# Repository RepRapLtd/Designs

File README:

This is just a dump of all my various designs for things that are not
specifically RepRap.

Some of the things here are OS designs that are not mine, and have just been placed
in this directory by me for convenience.

AB
24/2/2015

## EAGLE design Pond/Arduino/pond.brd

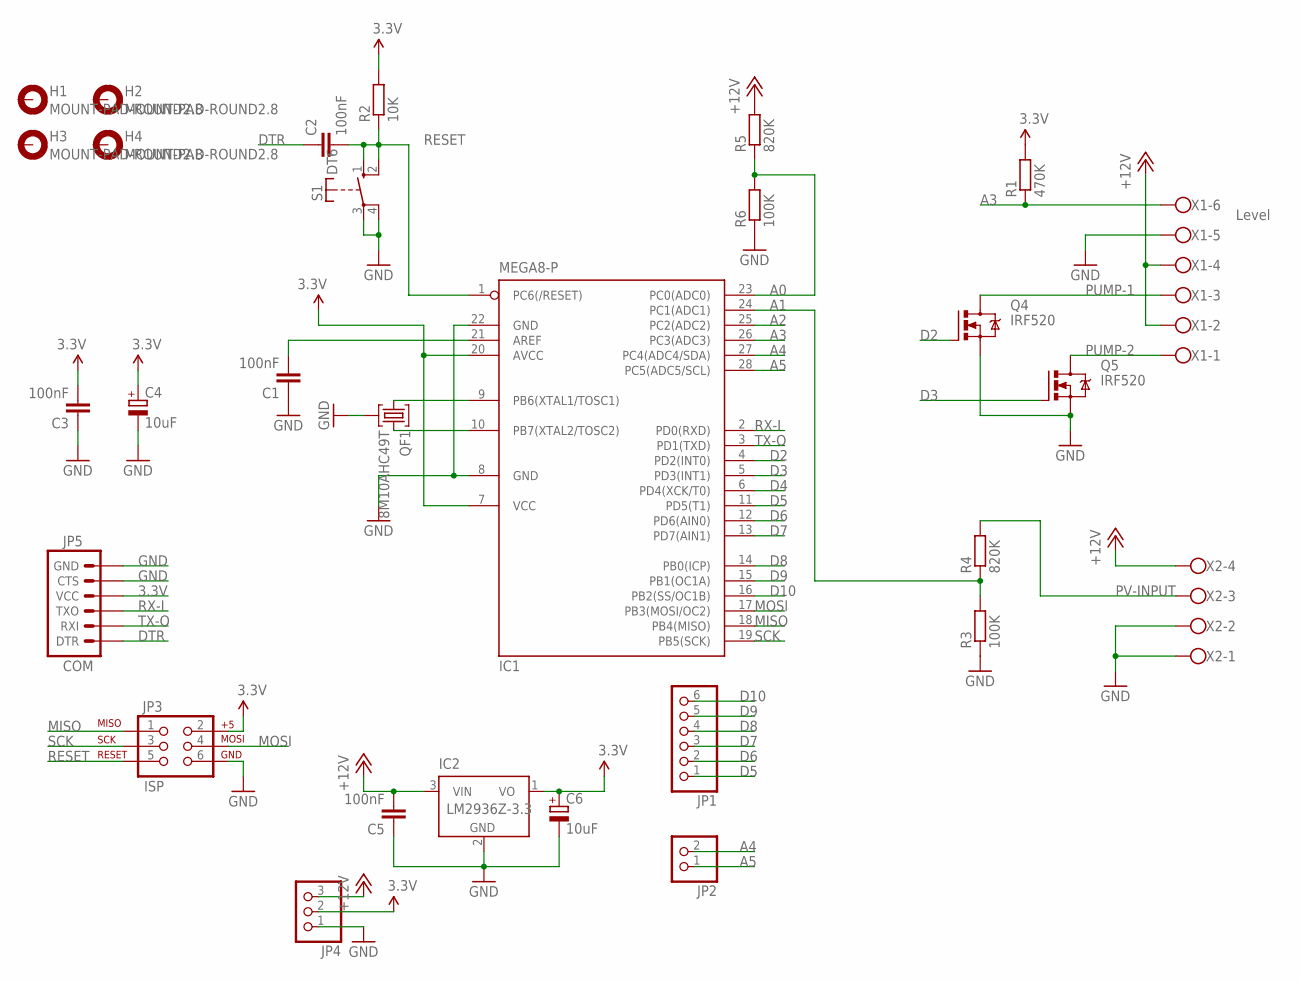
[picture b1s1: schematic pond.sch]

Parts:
C1, C2, C3, C5: 100nF; C050-050X075
C4, C6: 10uF; E2,5-6E
H1, H2, H3, H4: MOUNT-PAD-ROUND2.8; 2,8-PAD
IC1: MEGA8-P; DIL28-3
IC2: LM2936Z-3.3; TO92
JP1: PINHD-1X6; 1X06
JP2: PINHD-1X2; 1X02
JP3: ISP; 2X3
JP4: PINHD-1X3; 1X03
JP5: COM; 1X06
Q4, Q5: IRF520; TO220BV
QF1: 8M10AHC49T; HC49U
R1: 470K; 0207/10
R2: 10K; 0207/10
R3, R6: 100K; 0207/10
R4, R5: 820K; 0207/10
S1: DT6
X1: W237-6
X2: W237-4

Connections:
3.3V: C3.2, C4.+, C6.+, IC1.7 (VCC), IC1.20 (AVCC), IC2.1 (VO), JP3.2, JP4.2, JP5.4 (VCC), R1.2, R2.2
+12V: C5.2, IC2.3 (VIN), JP4.3, R5.2, X1.2, X1.4, X2.4
A0: IC1.23 (PC0(ADC0)), R5.1, R6.2
A1: IC1.24 (PC1(ADC1)), R3.2, R4.1
A2: IC1.25 (PC2(ADC2))
A3: IC1.26 (PC3(ADC3)), R1.1, X1.6
A4: IC1.27 (PC4(ADC4/SDA)), JP2.2
A5: IC1.28 (PC5(ADC5/SCL)), JP2.1
D2: IC1.4 (PD2(INT0)), Q4.G
D3: IC1.5 (PD3(INT1)), Q5.G
D4: IC1.6 (PD4(XCK/T0))
D5: IC1.11 (PD5(T1)), JP1.1
D6: IC1.12 (PD6(AIN0)), JP1.2
D7: IC1.13 (PD7(AIN1)), JP1.3
D8: IC1.14 (PB0(ICP)), JP1.4
D9: IC1.15 (PB1(OC1A)), JP1.5
D10: IC1.16 (PB2(SS/OC1B)), JP1.6
DTR: C2.1, JP5.1 (DTR)
GND: C1.1, C3.1, C4.-, C5.1, C6.-, IC1.8 (GND), IC1.22 (GND), IC2.2 (GND), JP3.6, JP4.1, JP5.5 (CTS), JP5.6 (GND), Q4.S, Q5.S, QF1.2, R3.1, R6.1, S1.3, S1.4, X1.5, X2.1, X2.2
MISO: IC1.18 (PB4(MISO)), JP3.1
MOSI: IC1.17 (PB3(MOSI/OC2)), JP3.4
unnamed: IC1.9 (PB6(XTAL1/TOSC1)), QF1.1
unnamed: IC1.10 (PB7(XTAL2/TOSC2)), QF1.3
unnamed: C1.2, IC1.21 (AREF)
PUMP-1: Q4.D, X1.3
PUMP-2: Q5.D, X1.1
PV-INPUT: R4.2, X2.3
RESET: C2.2, IC1.1 (PC6(/RESET)), JP3.5, R2.1, S1.1 (S), S1.2 (S)
RX-I: IC1.2 (PD0(RXD)), JP5.3 (TXO)
SCK: IC1.19 (PB5(SCK)), JP3.3
TX-O: IC1.3 (PD1(TXD)), JP5.2 (RXI)

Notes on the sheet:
Level

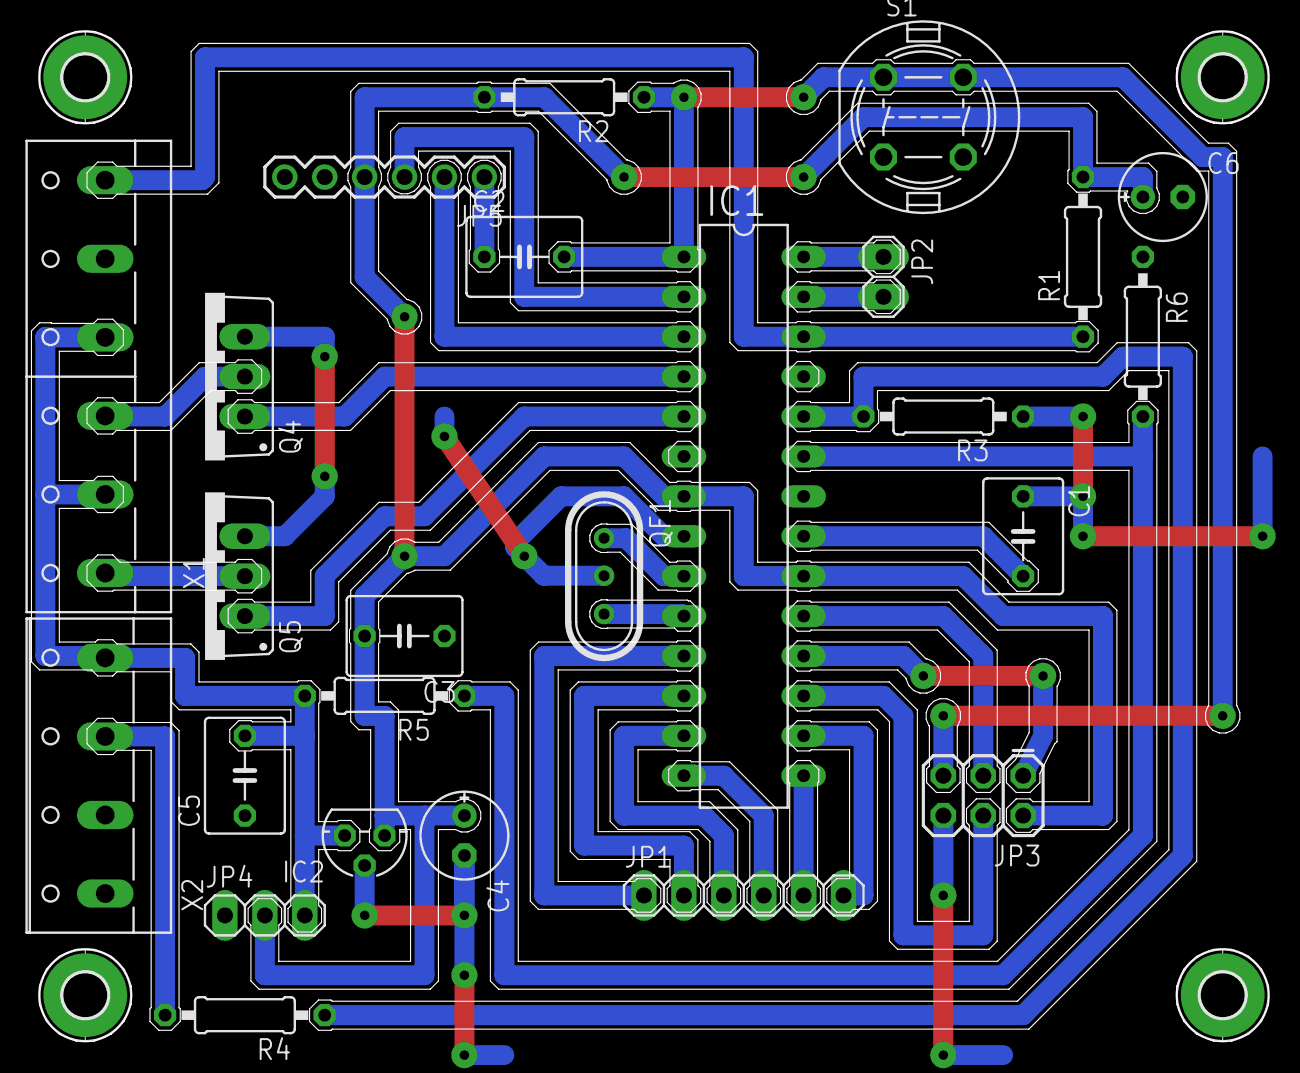
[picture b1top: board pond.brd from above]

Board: 2 copper layers, 78.7 x 64.3 mm, 29 parts (0 on the bottom side), 29 nets.

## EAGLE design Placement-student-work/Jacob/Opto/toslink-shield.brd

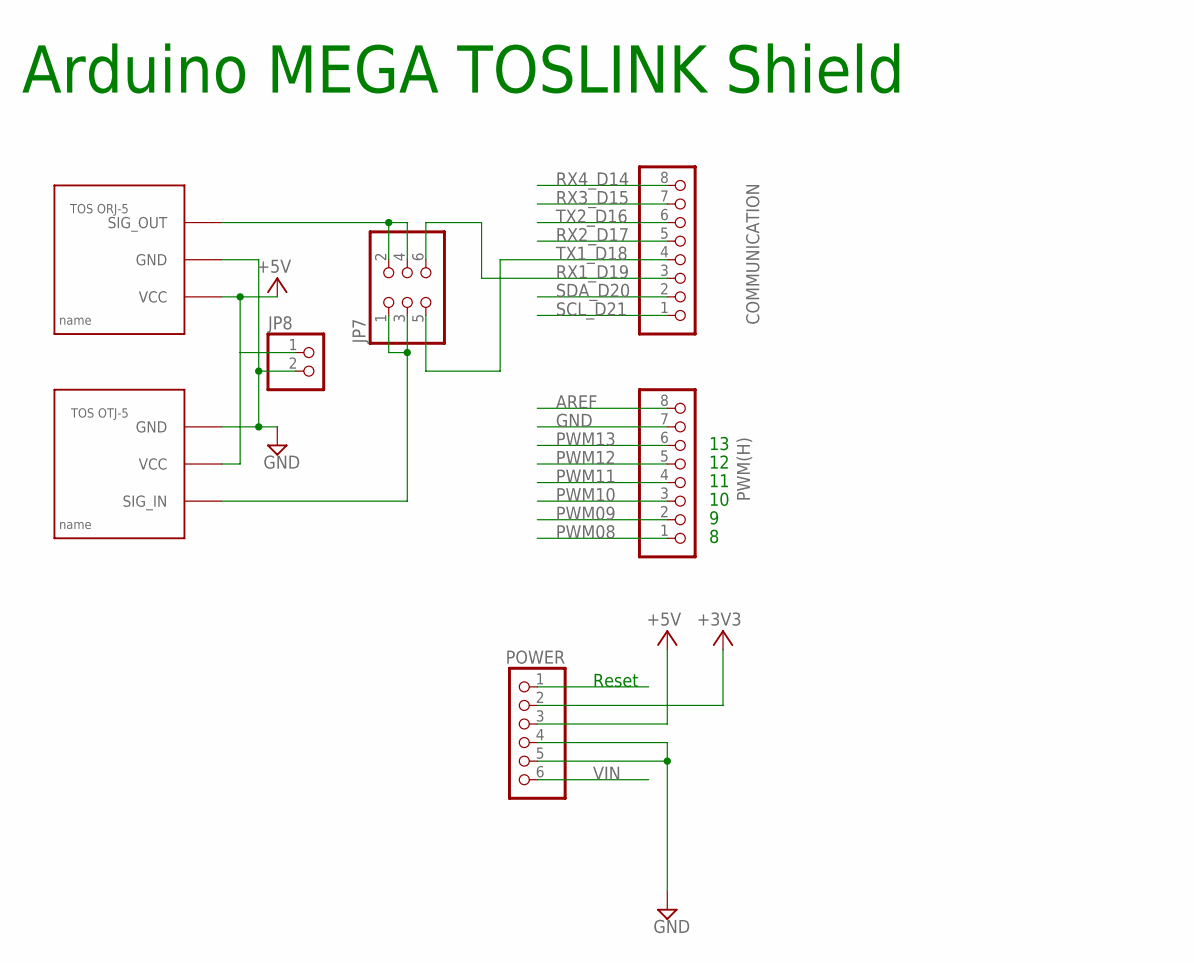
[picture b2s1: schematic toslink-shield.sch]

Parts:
COMMUNICATION: PINHD-1X8; 1X08
JP7: PINHD-2X3; 2X03
JP8: PINHD-1X2; 1X02
POWER: PINHD-1X6; 1X06
PWM(H): PINHD-1X8; 1X08
U$1: ORJ-5
U$2: OTJ-5

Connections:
+3V3: POWER.2
+5V: JP8.1, POWER.3, U$1.VCC, U$2.VCC
AREF: PWM(H).8
GND: JP8.2, POWER.4, POWER.5, PWM(H).7, U$1.GND, U$2.GND
unnamed: JP7.2, JP7.4, U$1.SIG_OUT
unnamed: JP7.1, JP7.3, U$2.SIG_IN
PWM08: PWM(H).1
PWM09: PWM(H).2
PWM10: PWM(H).3
PWM11: PWM(H).4
PWM12: PWM(H).5
PWM13: PWM(H).6
RESET: POWER.1
RX1_D19: COMMUNICATION.3, JP7.6
RX2_D17: COMMUNICATION.5
RX3_D15: COMMUNICATION.7
RX4_D14: COMMUNICATION.8
SCL_D21: COMMUNICATION.1
SDA_D20: COMMUNICATION.2
TX1_D18: COMMUNICATION.4, JP7.5
TX2_D16: COMMUNICATION.6
VIN: POWER.6

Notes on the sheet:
Arduino MEGA TOSLINK Shield
Reset

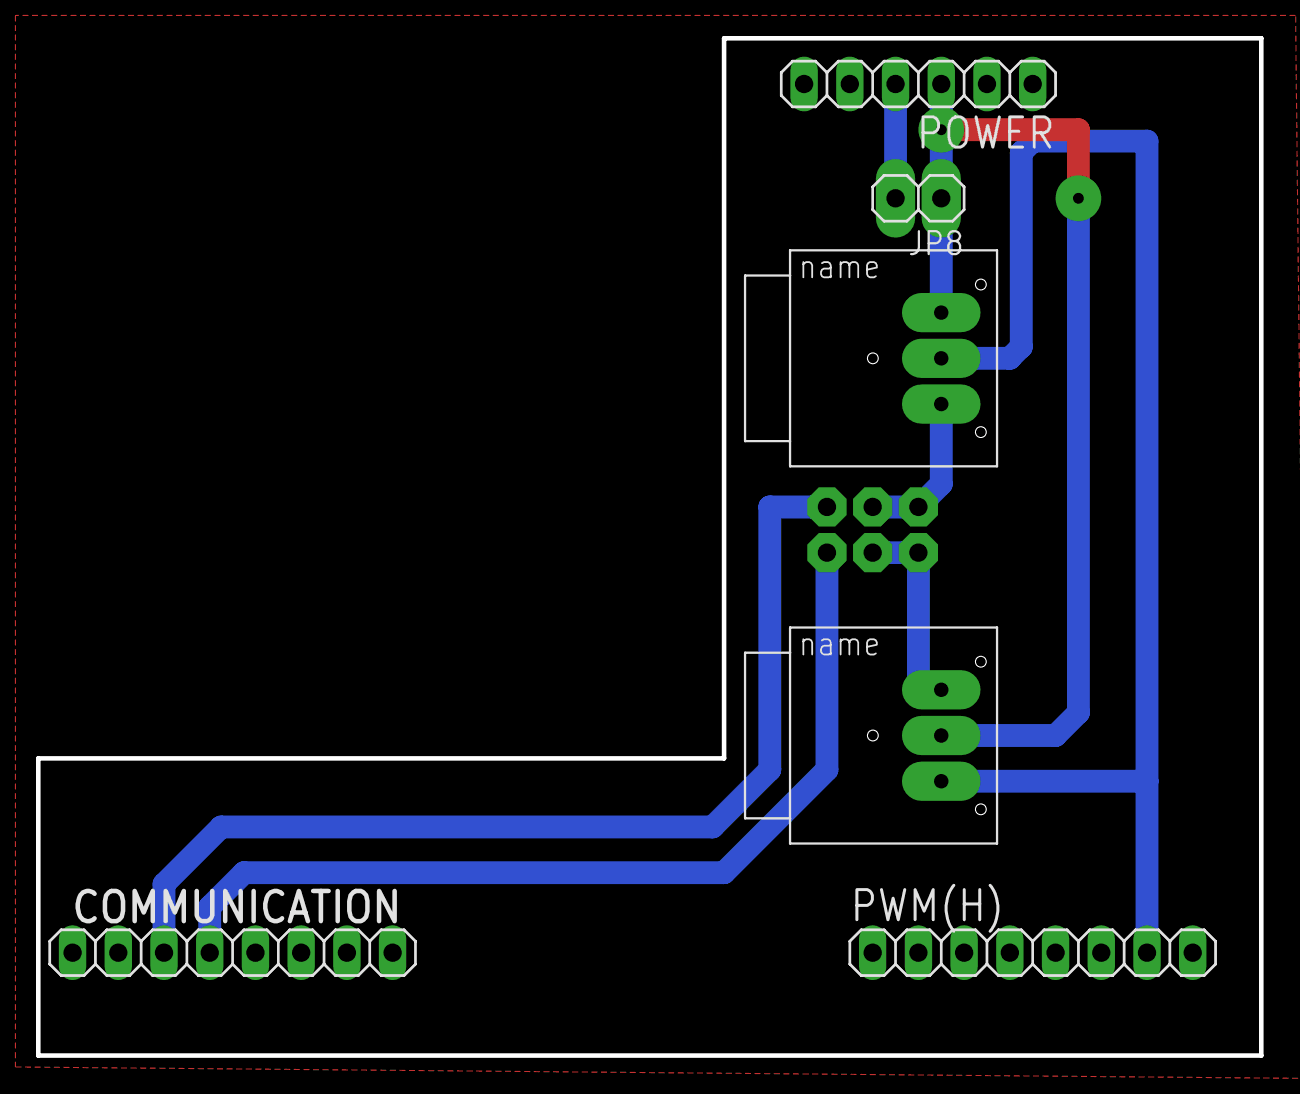
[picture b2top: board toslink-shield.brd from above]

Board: 2 copper layers, 67.9 x 56.5 mm, 7 parts (1 on the bottom side), 6 nets.

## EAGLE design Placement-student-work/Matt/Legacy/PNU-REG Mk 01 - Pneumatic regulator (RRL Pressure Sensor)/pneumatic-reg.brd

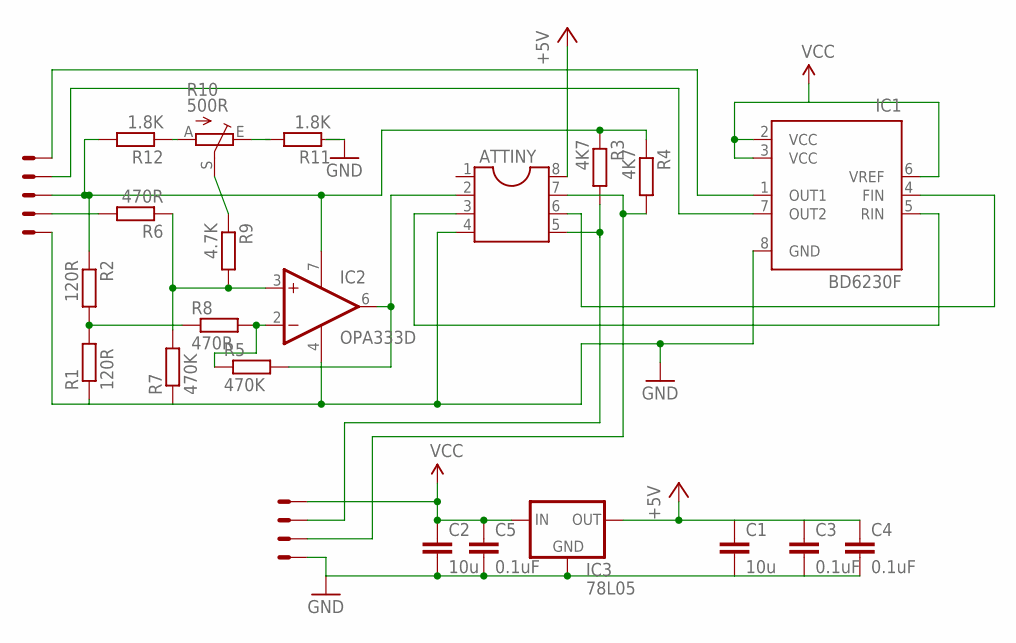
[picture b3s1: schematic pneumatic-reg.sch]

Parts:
ATTINY: DIL8; DIL08
C1, C2: 10u; C1206
C3, C4, C5: 0.1uF; C1206
IC1: BD6230F; SOP8
IC2: OPA333D; SO08
IC3: 78L05; 78LXX
R1, R2: 120R; M0805
R3, R4: 4K7; M0805
R5, R7: 470K; M0805
R6, R8: 470R; M0805
R9: 4.7K; M0805
R10: 500R; S64YW
R11, R12: 1.8K; M0805
X2: 22-23-2041
X7: 22-23-2051

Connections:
+5V: ATTINY.8, C1.1, C3.1, C4.1, IC2.7 (V+), IC3.OUT, R2.1, R3.1, R4.1, R12.2, X7.3
D0: ATTINY.3, IC1.5 (RIN)
D1: ATTINY.6, IC1.4 (FIN)
GND: ATTINY.4, C1.2, C2.2, C3.2, C4.2, C5.2, IC1.8 (GND), IC2.4 (V-), IC3.GND, R1.1, R7.1, X2.1, X7.1
unnamed: R1.2, R2.2, R8.1
unnamed: ATTINY.5, R3.2, X2.3
unnamed: IC1.7 (OUT2), X7.4
unnamed: IC1.1 (OUT1), X7.5
unnamed: ATTINY.2, IC2.6 (OUT), R5.2
unnamed: IC2.2 (-IN), R5.1, R8.2
unnamed: ATTINY.7, R4.2, X2.2
unnamed: R10.A, R12.1
unnamed: R6.2, X7.2
unnamed: IC2.3 (+IN), R6.1, R7.2, R9.2
unnamed: R9.1, R10.S
VCC: C2.1, C5.1, IC1.2 (VCC), IC1.3 (VCC), IC1.6 (VREF), IC3.IN, X2.4

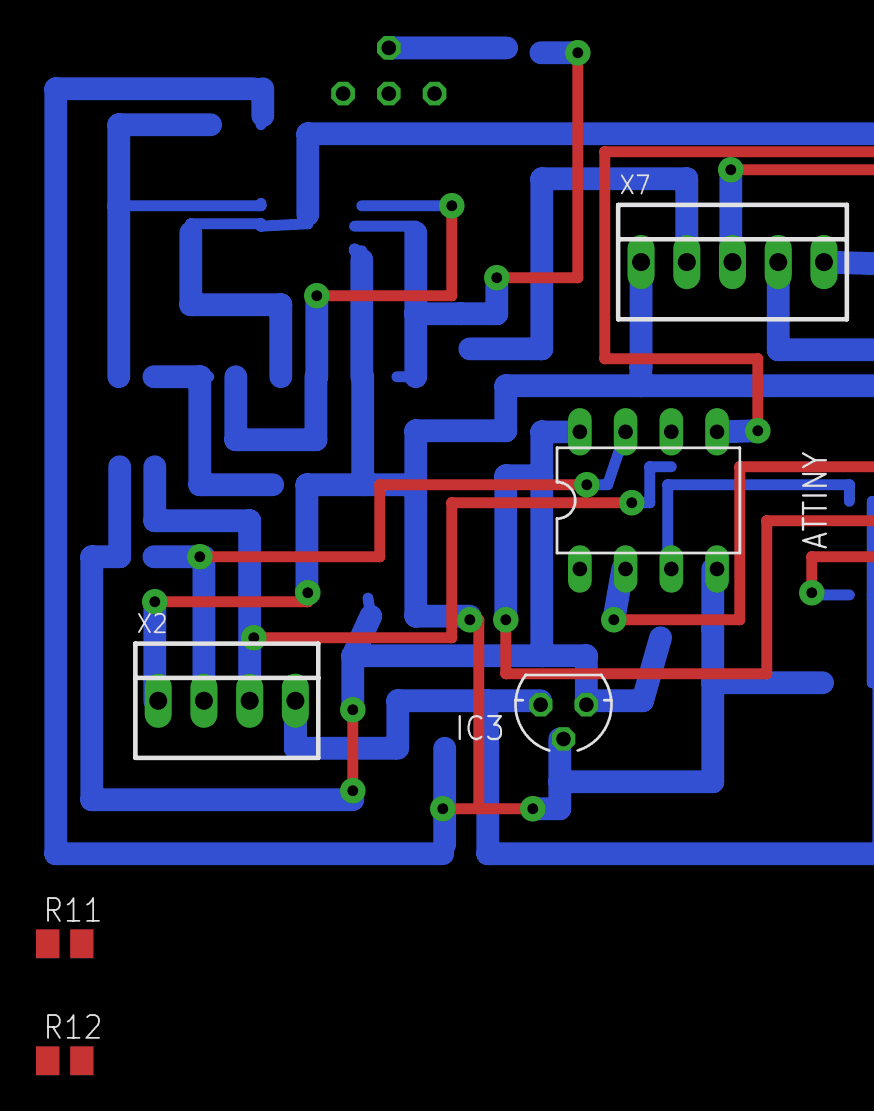
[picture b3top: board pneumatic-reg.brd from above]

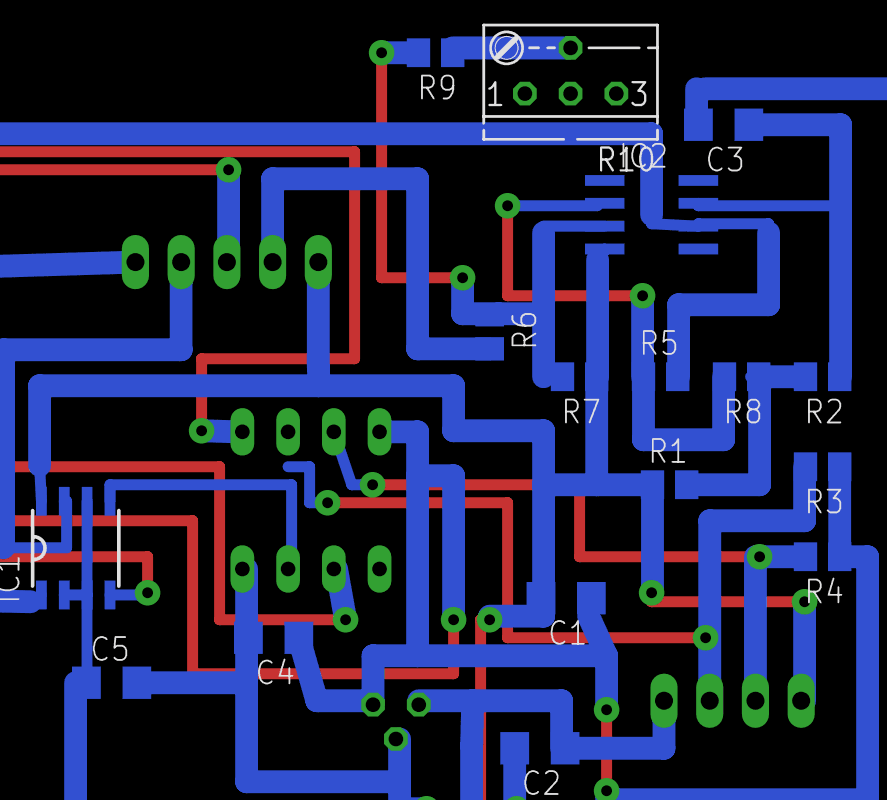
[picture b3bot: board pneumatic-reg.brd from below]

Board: 2 copper layers, 23 parts (17 on the bottom side), 16 nets.

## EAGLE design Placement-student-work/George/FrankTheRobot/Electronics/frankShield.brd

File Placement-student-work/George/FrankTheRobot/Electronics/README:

The files in this directory called frankShield.sch and frankshield.brd are the Eagle schematic and PCB layout for the Adruino shield for Frank the Robot.

They are intended to go with an EPS8266 D1 Arduino-pinout WiFi controller, which operates at 3V3. On no account use it with any board operating at 5V.

The directory Data-sheets contains .PDF files for some of the components used.

The directory Legacy-files contains previous designs and experiments.

The file pcbtrain.dru contains the Eagle design-rules file from http://optics.eee.nottingham.ac.uk/eagle/eagle2pcbtrain.html

The file frank-gerb274x.cam is the Eagle job that generates the GERBER files for the PCB.

The file clean is a short shell script that removes the Eagle temporary files.

The GERBER files for the board are in the CAM directory.  They have the subscripts:

.GTL - top copper
.GBL - bottom copper
.GTO - top silkscreen
.GTP - top paste
.GBO - bottom silkscreen (this is not needed)
.GTS - top soldermask
.GBS - bottom soldermask
.TXT - drill file
.dri - drill specifications
.GML - Mill layer (this is not needed)

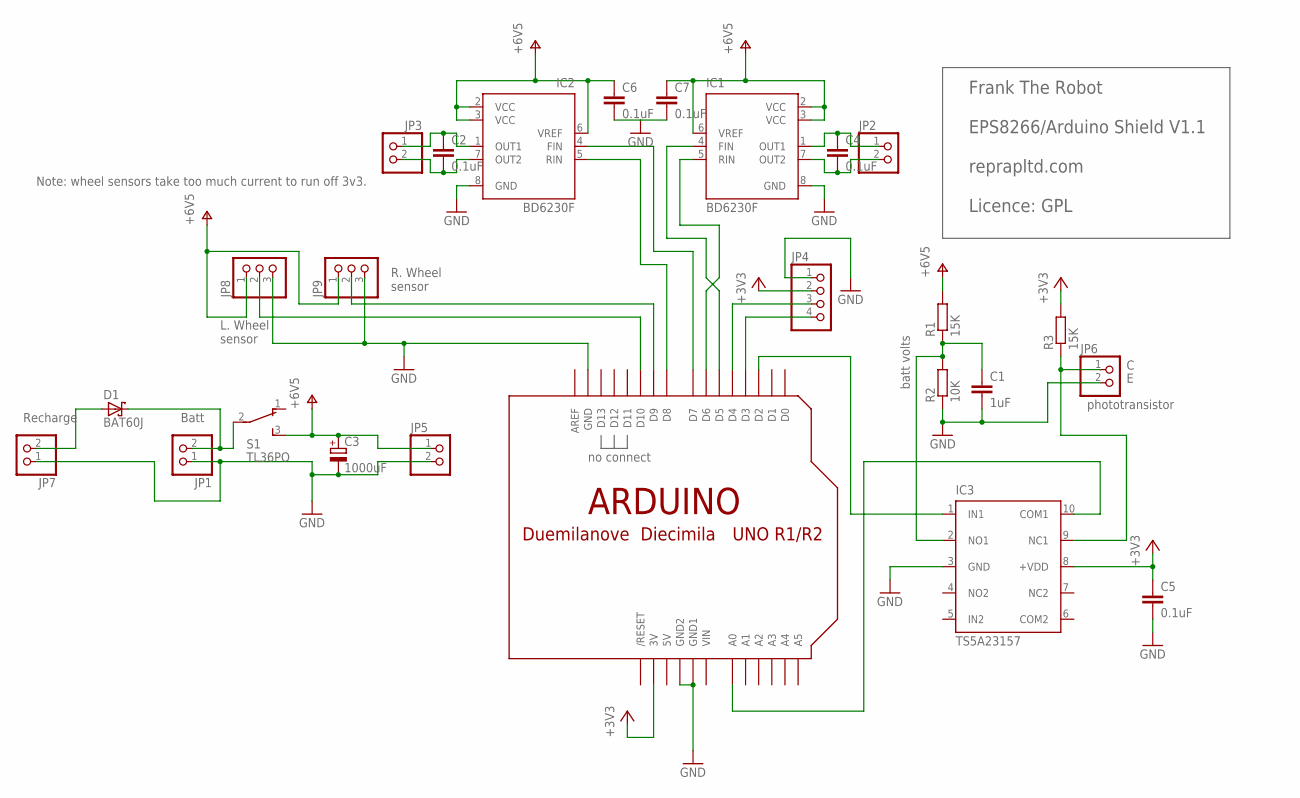
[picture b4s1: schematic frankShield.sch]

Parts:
C1: 1uF; C0805
C2, C4, C5, C6, C7: 0.1uF; C0805
C3: 1000uF; B45181B
D1: BAT60J; SOD323_ST
IC1, IC2: BD6230F; SOP8
IC3: TS5A23157; MSOP10
JP1, JP2, JP3, JP5, JP6, JP7: PINHD-1X2; 1X02
JP4: PINHD-1X4; 1X04
JP8, JP9: PINHD-1X3; 1X03
R1, R3: 15K; M0805
R2: 10K; M0805
S1: TL36PO; TL3XPO
U$1: ARDUINO-BPLACE

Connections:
5V: U$1.5V
+3V3: C5.1, IC3.8 (+VDD), JP4.2, R3.2, U$1.3V
GND: C1.2, C3.-, C5.2, C6.2, C7.2, IC1.8 (GND), IC2.8 (GND), IC3.3 (GND), JP1.1, JP4.1, JP5.2, JP6.2, JP7.1, JP8.3, JP9.3, R2.1, U$1.GND, U$1.GND1, U$1.GND2
unnamed: JP4.4, U$1.D3
unnamed: JP4.3, U$1.D4
unnamed: C2.1, IC2.1 (OUT1), JP3.1
unnamed: C2.2, IC2.7 (OUT2), JP3.2
unnamed: C4.1, IC1.1 (OUT1), JP2.1
unnamed: C4.2, IC1.7 (OUT2), JP2.2
unnamed: IC1.5 (RIN), U$1.D6
unnamed: IC1.4 (FIN), U$1.D5
unnamed: IC2.4 (FIN), U$1.D7
unnamed: IC2.5 (RIN), U$1.D8
unnamed: IC3.10 (COM1), U$1.A0
unnamed: C1.1, IC3.2 (NO1), R1.1, R2.2
unnamed: D1.C, JP1.2, S1.2
unnamed: IC3.9 (NC1), JP6.1, R3.1
unnamed: IC3.1 (IN1), U$1.D2
unnamed: D1.A, JP7.2
unnamed: JP9.2, U$1.D9
unnamed: JP8.2, U$1.D10
NC2: IC3.7 (NC2)
V+: C3.+, C6.1, C7.1, IC1.2 (VCC), IC1.3 (VCC), IC1.6 (VREF), IC2.2 (VCC), IC2.3 (VCC), IC2.6 (VREF), JP5.1, JP8.1, JP9.1, R1.2, S1.3 (S)
VIN: U$1.VIN

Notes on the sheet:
phototransistor
Frank The Robot EPS8266/Arduino Shield V1.1 reprapltd.com Licence: GPL
Batt
Recharge
L. Wheel sensor
R. Wheel sensor
batt volts
Note: wheel sensors take too much current to run off 3v3.
no connect

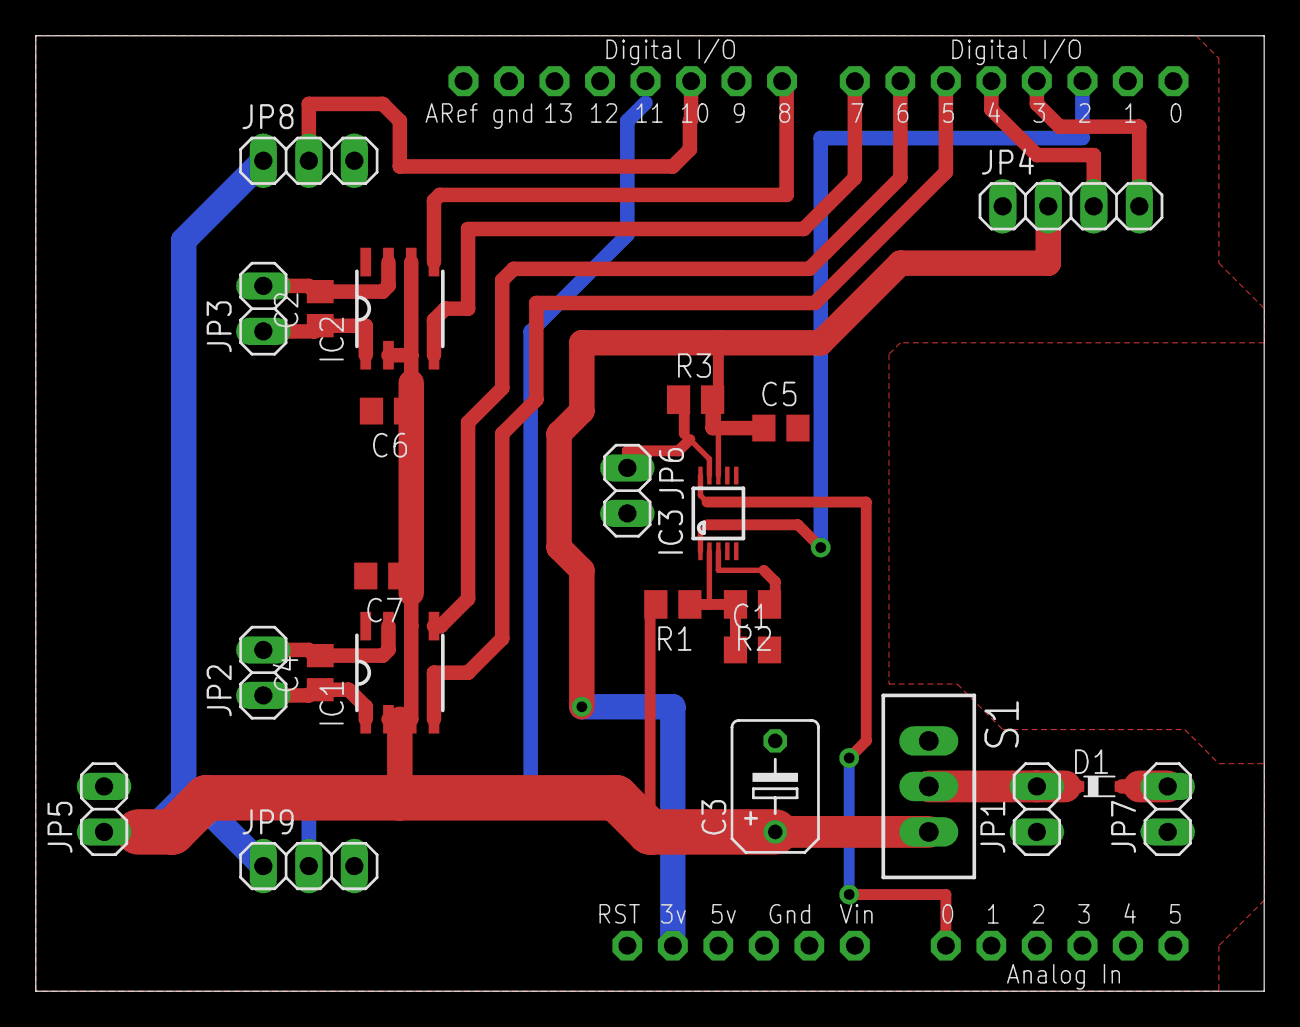
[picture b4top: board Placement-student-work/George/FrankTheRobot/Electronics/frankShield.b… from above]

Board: 2 copper layers, 68.6 x 53.3 mm, 25 parts (0 on the bottom side), 21 nets.

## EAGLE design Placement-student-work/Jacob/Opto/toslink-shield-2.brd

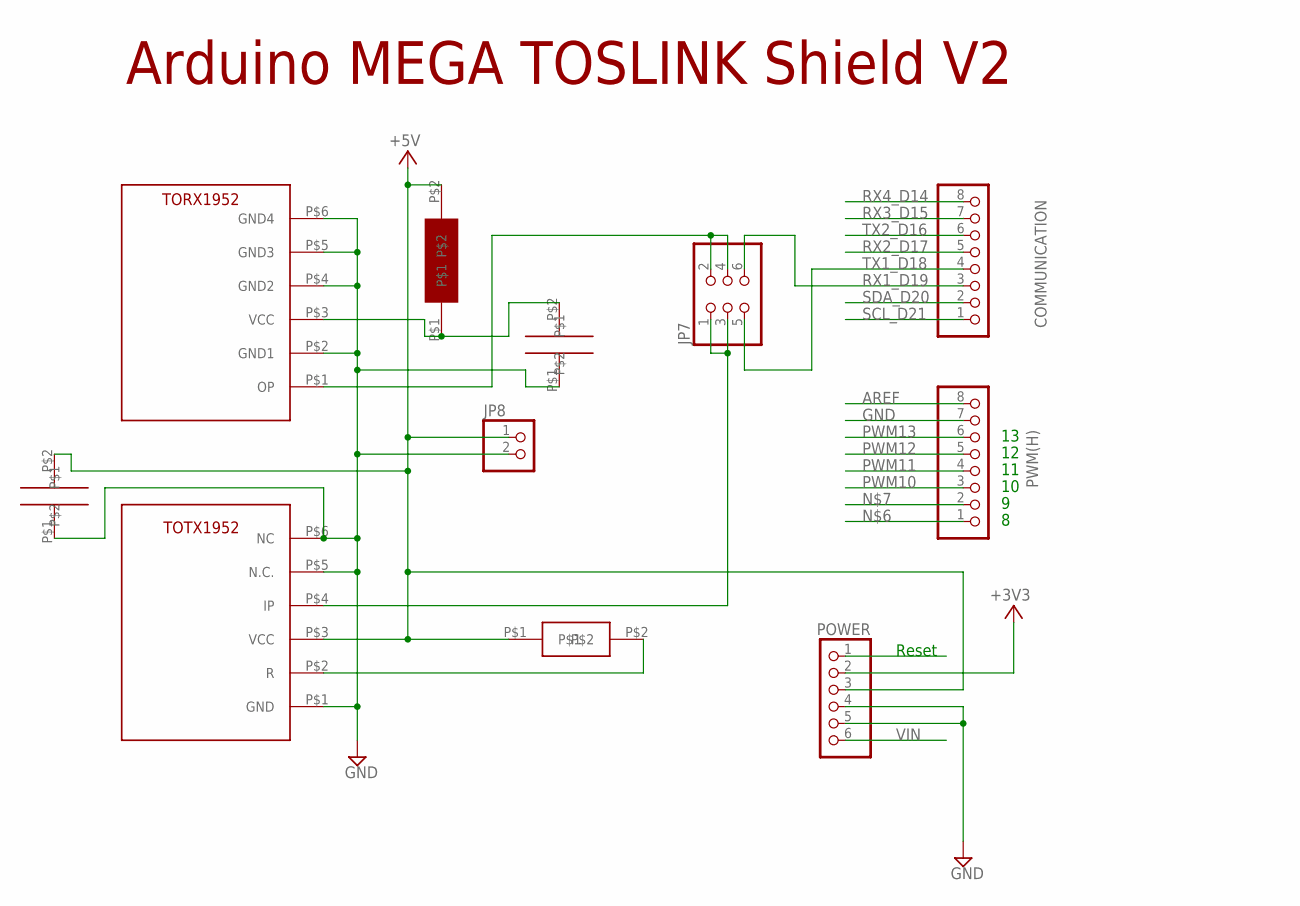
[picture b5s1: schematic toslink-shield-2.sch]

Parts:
COMMUNICATION: PINHD-1X8; 1X08
JP7: PINHD-2X3; 2X03
JP8: PINHD-1X2; 1X02
POWER: PINHD-1X6; 1X06
PWM(H): PINHD-1X8; 1X08
U$1: TORX1952
U$2: TOTX1952
U$3: 47uH; L-0.1
U$4: 100nF; C-0.1
U$5: C-0.1
U$6: -0.2; R-0.2

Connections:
+3V3: POWER.2
AREF: PWM(H).8
GND: JP8.2, POWER.4, POWER.5, PWM(H).7, U$1.P$2 (GND1), U$1.P$4 (GND2), U$1.P$5 (GND3), U$1.P$6 (GND4), U$2.P$1 (GND), U$2.P$5 (N.C.), U$2.P$6 (NC), U$4.P$1, U$5.P$1
unnamed: JP7.2, JP7.4, U$1.P$1 (OP)
unnamed: JP7.1, JP7.3, U$2.P$4 (IP)
unnamed: U$2.P$2 (R), U$6.P$2
unnamed: U$1.P$3 (VCC), U$3.P$1, U$4.P$2
unnamed: JP8.1, POWER.3, U$2.P$3 (VCC), U$3.P$2, U$5.P$2, U$6.P$1
PWM10: PWM(H).3
PWM11: PWM(H).4
PWM12: PWM(H).5
PWM13: PWM(H).6
RESET: POWER.1
RX1_D19: COMMUNICATION.3, JP7.6
RX2_D17: COMMUNICATION.5
RX3_D15: COMMUNICATION.7
RX4_D14: COMMUNICATION.8
SCL_D21: COMMUNICATION.1
SDA_D20: COMMUNICATION.2
TX1_D18: COMMUNICATION.4, JP7.5
TX2_D16: COMMUNICATION.6
VIN: POWER.6

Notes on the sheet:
Arduino MEGA TOSLINK Shield V2
Reset

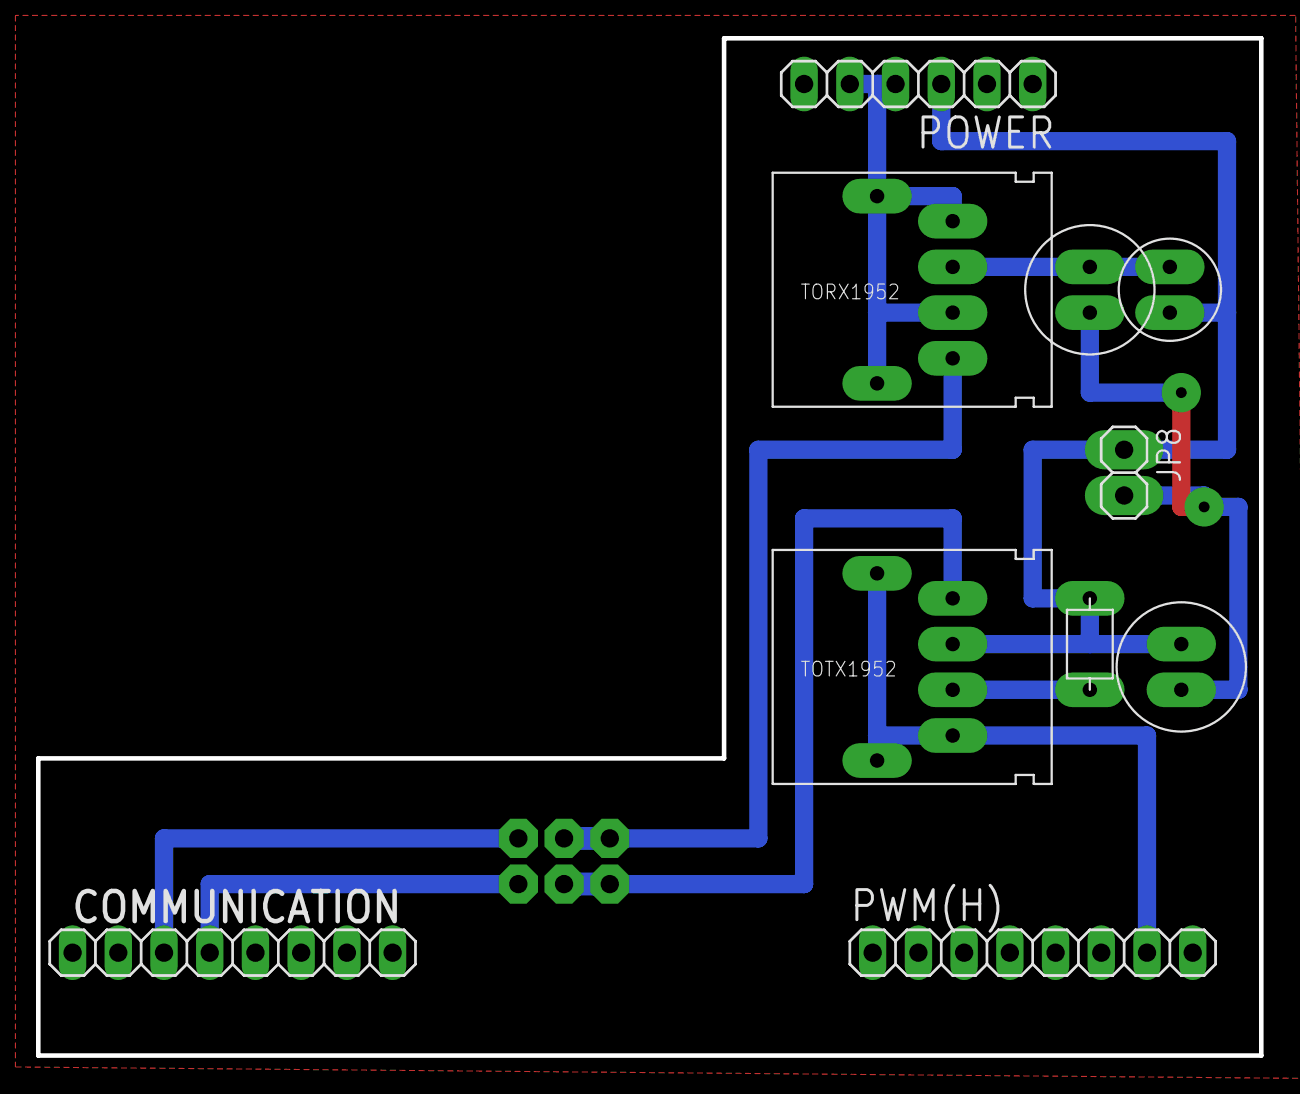
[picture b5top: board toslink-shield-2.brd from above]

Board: 2 copper layers, 67.9 x 56.5 mm, 11 parts (1 on the bottom side), 8 nets.

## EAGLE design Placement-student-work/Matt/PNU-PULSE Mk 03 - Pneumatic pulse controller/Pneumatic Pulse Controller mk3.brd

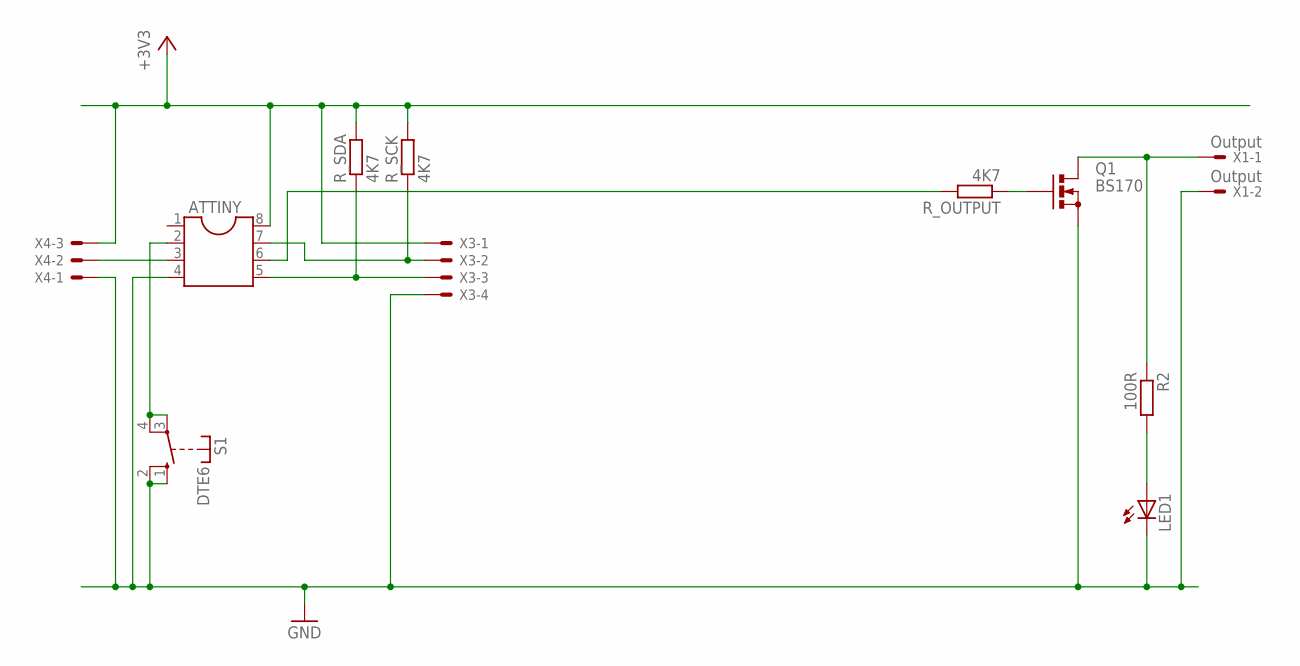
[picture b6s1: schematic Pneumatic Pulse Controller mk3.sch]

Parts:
ATTINY: DIL8; DIL08
LED1: LED3MM
Q1: BS170; SOT54E
R2: 100R; 0204/7
R_OUTPUT: 4K7; M0805
R_SCK: 4K7; M0805
R_SDA: 4K7; M0805
S1: DTE6
X1: Output; KK-156-2
X3: KK-156-4
X4: KK-156-3

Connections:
+3V3: ATTINY.8, R_SCK.2, R_SDA.2, X3.1, X4.3
GND: ATTINY.4, LED1.K (C), Q1.S, S1.1 (S), S1.2 (S), X1.2, X3.4, X4.1
unnamed: Q1.G, R_OUTPUT.1
unnamed: Q1.D, R2.1, X1.1
unnamed: ATTINY.3, X4.2
unnamed: LED1.A, R2.2
SCK: ATTINY.7, R_SCK.1, X3.2
SDA: ATTINY.5, R_SDA.1, X3.3
SWITCH: ATTINY.2, S1.3, S1.4
VOUT: ATTINY.6, R_OUTPUT.2

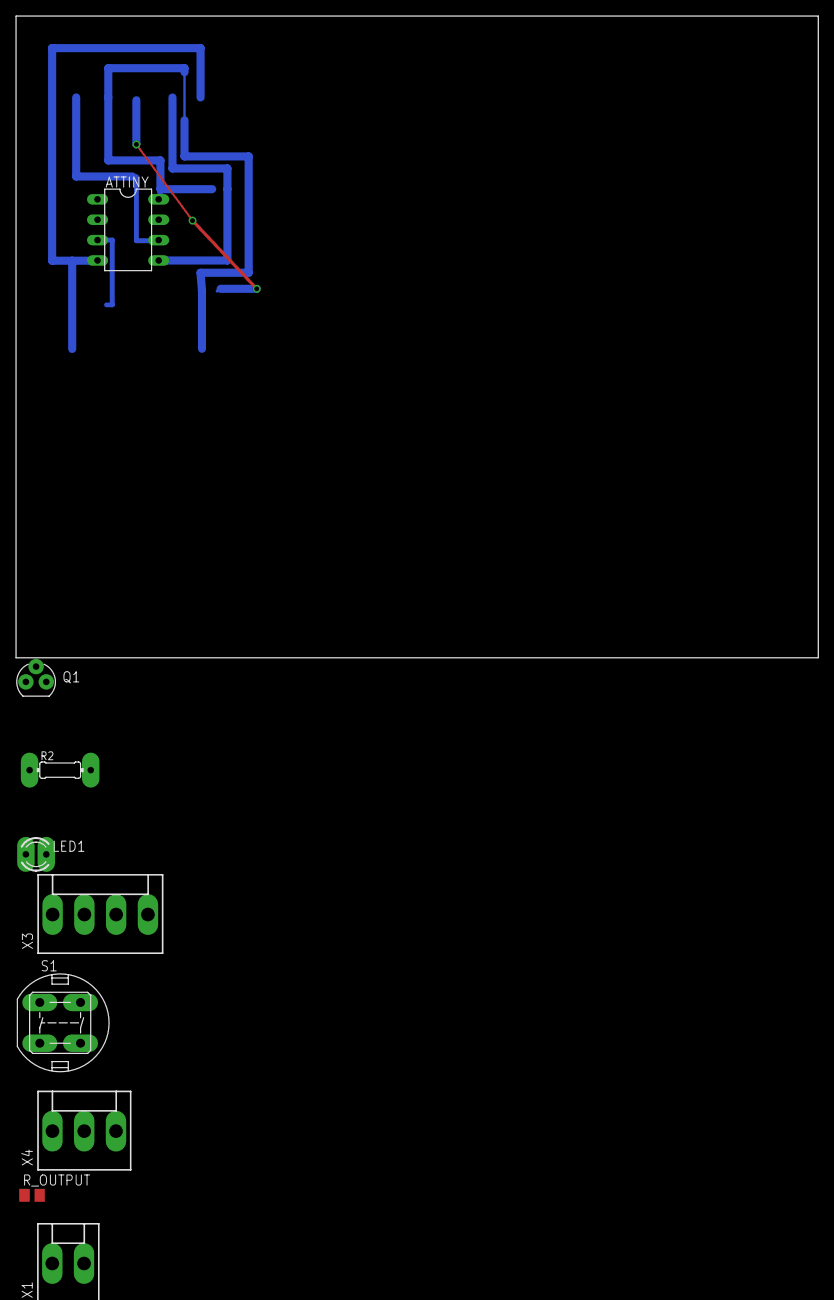
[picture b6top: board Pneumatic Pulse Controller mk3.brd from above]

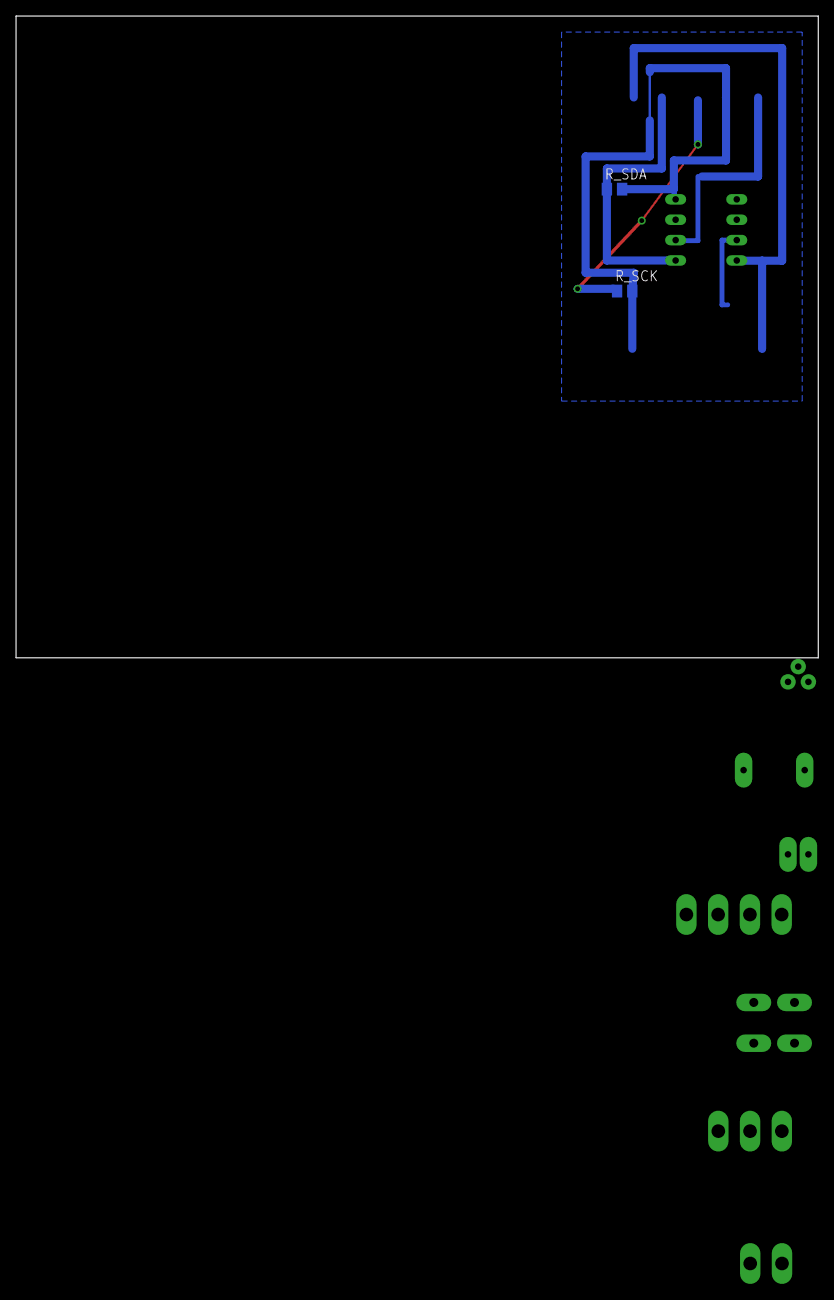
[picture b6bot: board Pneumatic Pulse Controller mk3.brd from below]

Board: 2 copper layers, 100.0 x 80.0 mm, 11 parts (2 on the bottom side), 10 nets.

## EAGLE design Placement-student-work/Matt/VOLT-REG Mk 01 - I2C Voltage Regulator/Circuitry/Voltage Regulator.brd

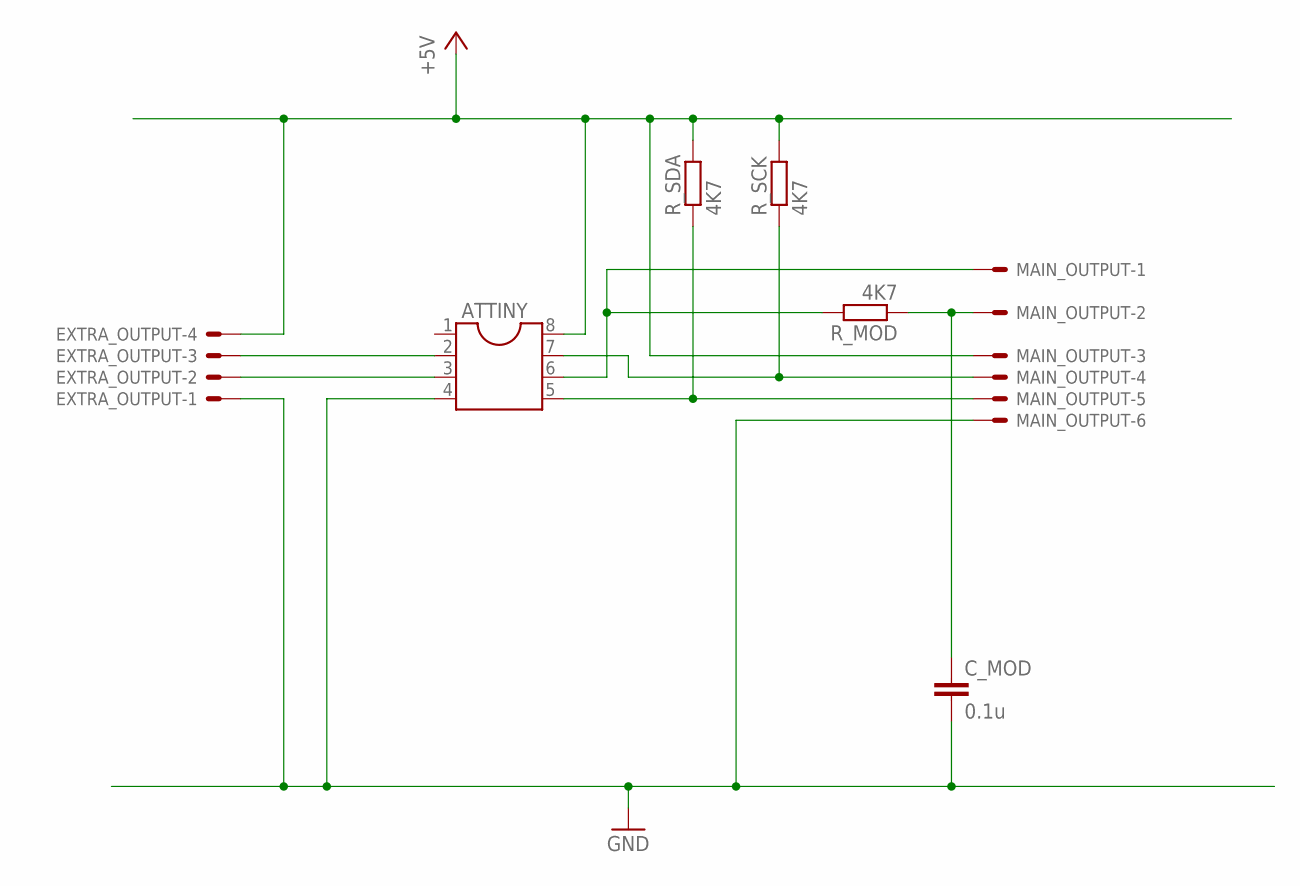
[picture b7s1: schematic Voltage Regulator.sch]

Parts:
ATTINY: DIL8; DIL08
C_MOD: 0.1u; C1206
EXTRA_OUTPUT: KK-156-4
MAIN_OUTPUT: KK-156-6
R_MOD: 4K7; M0805
R_SCK: 4K7; M0805
R_SDA: 4K7; M0805

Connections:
+5V: ATTINY.8, EXTRA_OUTPUT.4, MAIN_OUTPUT.3, R_SCK.2, R_SDA.2
GND: ATTINY.4, C_MOD.2, EXTRA_OUTPUT.1, MAIN_OUTPUT.6
unnamed: ATTINY.2, EXTRA_OUTPUT.3
unnamed: ATTINY.3, EXTRA_OUTPUT.2
SCK: ATTINY.7, MAIN_OUTPUT.4, R_SCK.1
SDA: ATTINY.5, MAIN_OUTPUT.5, R_SDA.1
V_ANG: C_MOD.1, MAIN_OUTPUT.2, R_MOD.1
V_PWM: ATTINY.6, MAIN_OUTPUT.1, R_MOD.2

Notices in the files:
parts and their libraries:
SparkFun: Licensing: CC v3.0 Share-Alike You are welcome to use this library for commercial purposes.
